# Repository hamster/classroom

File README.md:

# hamster university

This repo contains classroom materials I have developed.

## Firwmare 101

[This class](/Firmware101) is aimed at beginners who want a no-code introduction to firmware development.  Don't expect to absorb all the info presented here, instead just try to get a feel for all the parts of the overall system.  Future classes will work on getting you comfortable with these bits.

[Here's a link](https://www.youtube.com/watch?v=nslHeXYYATM) to me presenting this material at the DC801 hackerspace in Salt Lake City, Utah

## Firmware 102

[This class](/Firmware102) is aimed at beginners that want to learn how to develop and program an Arduino in a 'novel' way - by not using the Arduino IDE.  The goal is to teach how some of the low level interfacing and programming is handled without the Arduino IDE magicking away all the fun bits.

There is some required hardware for the class - follow the [link](/Firmware102) to the class files to learn more.

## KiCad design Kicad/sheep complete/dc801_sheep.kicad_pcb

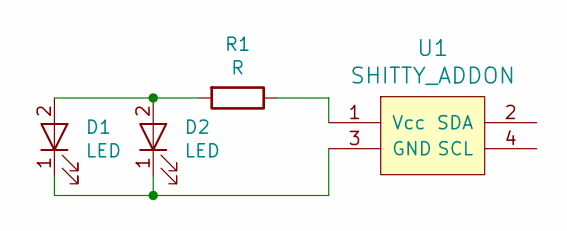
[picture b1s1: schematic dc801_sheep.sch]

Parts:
D1, D2: LED; 0807-RGB
R1: R; R_0805_2012Metric_Pad1.15x1.50mm_HandSolder
U1: SHITTY_ADDON; Badgelife-Shitty-2x2-NotRotated

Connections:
unnamed: D1.1 (K), D2.1 (K), U1.3 (GND)
unnamed: D1.2 (A), D2.2 (A), R1.2
unnamed: R1.1, U1.1 (Vcc)

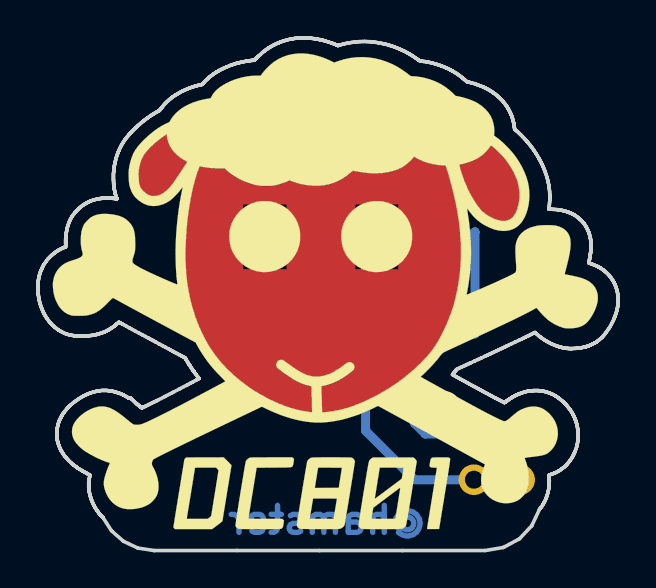
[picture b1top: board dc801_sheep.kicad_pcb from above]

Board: 2 copper layers, 32.2 x 28.5 mm, 4 parts (1 on the bottom side), 3 nets.

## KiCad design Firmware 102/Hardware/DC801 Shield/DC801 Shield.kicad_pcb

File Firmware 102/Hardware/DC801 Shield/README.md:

## DC801 Arduino Shield

# BOM

Prices/sourcing as of 2/2018

Item | Part Number | Sourcing | Cost Each (100 unit pricing) | Needed per kit | Total
-----|-------------|----------|------------------------------|----------------|------
PCB | 100 qty, black silkscreen | [seeed](https://www.seeedstudio.com/fusion_pcb.html) | | 1 | 
SW1,2 | TL3305AF260QG | [digikey](https://www.digikey.com/scripts/DkSearch/dksus.dll?Detail&itemSeq=252764681&uq=636549402931428208) | 0.16550 | 2 | 0.33
D1,2 | CLV1L-FKB-CHMMQEHBB7673673 | [digikey](https://www.digikey.com/scripts/DkSearch/dksus.dll?Detail&itemSeq=252763847&uq=636549402931418208) | 0.30360 | 2 | 0.60
D3-6 | 150080YS75000 | [digikey](https://www.digikey.com/scripts/DkSearch/dksus.dll?Detail&itemSeq=252763859&uq=636549402931418208) | 0.13700 | 4 | 0.55
R1-10 | RC0805JR-07150RL | [digikey](https://www.digikey.com/scripts/DkSearch/dksus.dll?Detail&itemSeq=252764725&uq=636549402931428208) | 0.00760 | 10 | 0.08
Headers | 1x10, 2x8, 1x6 | | | | |
Total | Per each board kit | | | | $1.56

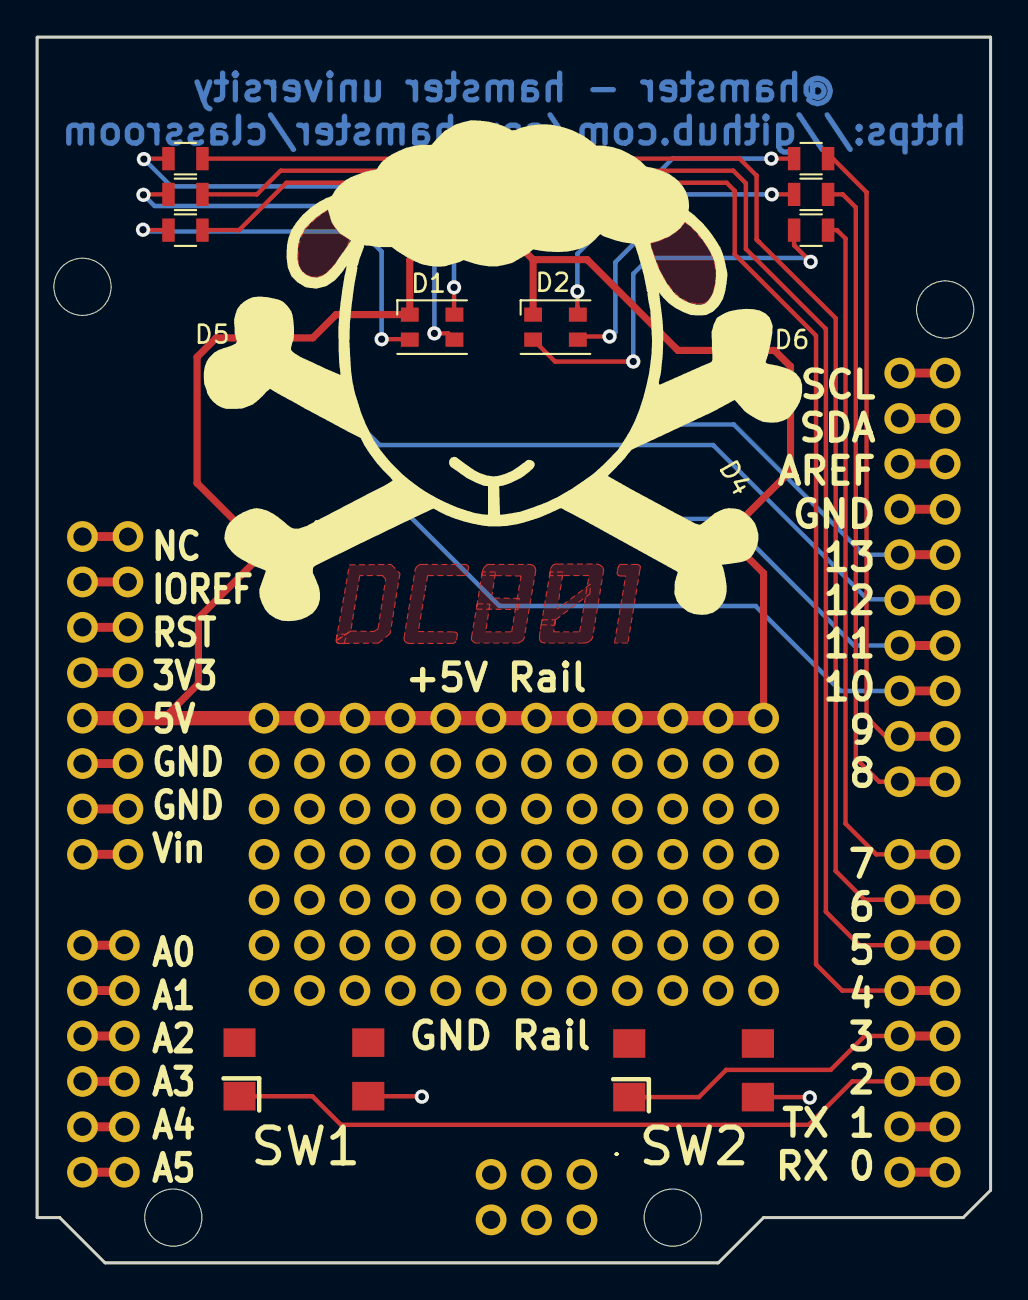
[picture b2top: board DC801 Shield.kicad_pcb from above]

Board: 2 copper layers, 53.4 x 68.6 mm, 19 parts (0 on the bottom side), 24 nets.

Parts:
D1, D2: LED_RABG; LED_Cree-PLCC4_3.2x2.8mm_CCW
D3, D4, D5, D6: LED; LED_0805
R1, R2, R3, R4, R5, R6, R7, R8, R9, R10: 150; R_0805
SW1, SW2: SW_Push; TL3305_Switch
XA1: Arduino_Uno_Shield

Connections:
+5V: D1.1, D2.1, D3.2, D4.2, D5.2, D6.2, XA1.5V1
GNDREF: SW1.2, SW2.2, XA1.GND1, XA1.GND2, XA1.GND3
unnamed: D1.2, R1.1
unnamed: D1.3, R2.1
unnamed: D1.4, R3.1
unnamed: D2.2, R4.1
unnamed: D2.3, R5.1
unnamed: D2.4, R6.1
unnamed: D3.1, R7.1
unnamed: D4.1, R8.1
unnamed: D5.1, R9.1
unnamed: D6.1, R10.1
unnamed: R1.2, XA1.D4
unnamed: R2.2, XA1.D5
unnamed: R3.2, XA1.D6
unnamed: R4.2, XA1.D7
unnamed: R5.2, XA1.D8
unnamed: R6.2, XA1.D9
unnamed: R7.2, XA1.D10
unnamed: R8.2, XA1.D11
unnamed: R9.2, XA1.D12
unnamed: R10.2, XA1.D13
unnamed: SW1.1, XA1.D2
unnamed: SW2.1, XA1.D3

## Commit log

2017-12-04 Adding the Firmware 101 class
2017-12-04 Fixing link to logo
2018-02-23 Adding a stub for Firmware 102
2018-02-23 Finished routing, adding images
2018-03-26 Update readme and images
2018-03-26 Renamed folders
2018-04-06 Adding the presentation and class code Adding gerbers for the shield Adding a simplified schematic for the shield-uno interface Updated KiCad stuff to 5.0 KiCad
2019-08-22 Adding presentations at DC801 and defcon HHV for getting started with KiCad
2020-02-11 Adding intro class to SMPS
2020-02-11 Adding ohms law slide and cleaning up some others
2024-04-03 Adding talks folder
2024-04-04 Final draft, to be reviewed
2024-08-08 Stubbing out badge post production talk
2024-08-09 Update SSTV talk with as-presented at defcon 32
2024-08-10 Fleshed out badge delivery slides
2025-04-25 Adding Weather Sat talk draft
2025-08-06 Updated weather sat talk for dczia
2025-08-06 Updated weather sat talk for defcon 33
2025-08-07 Adding PCB panelization talk for defcon 33
2025-10-23 Adding Logic Analyzer talk
